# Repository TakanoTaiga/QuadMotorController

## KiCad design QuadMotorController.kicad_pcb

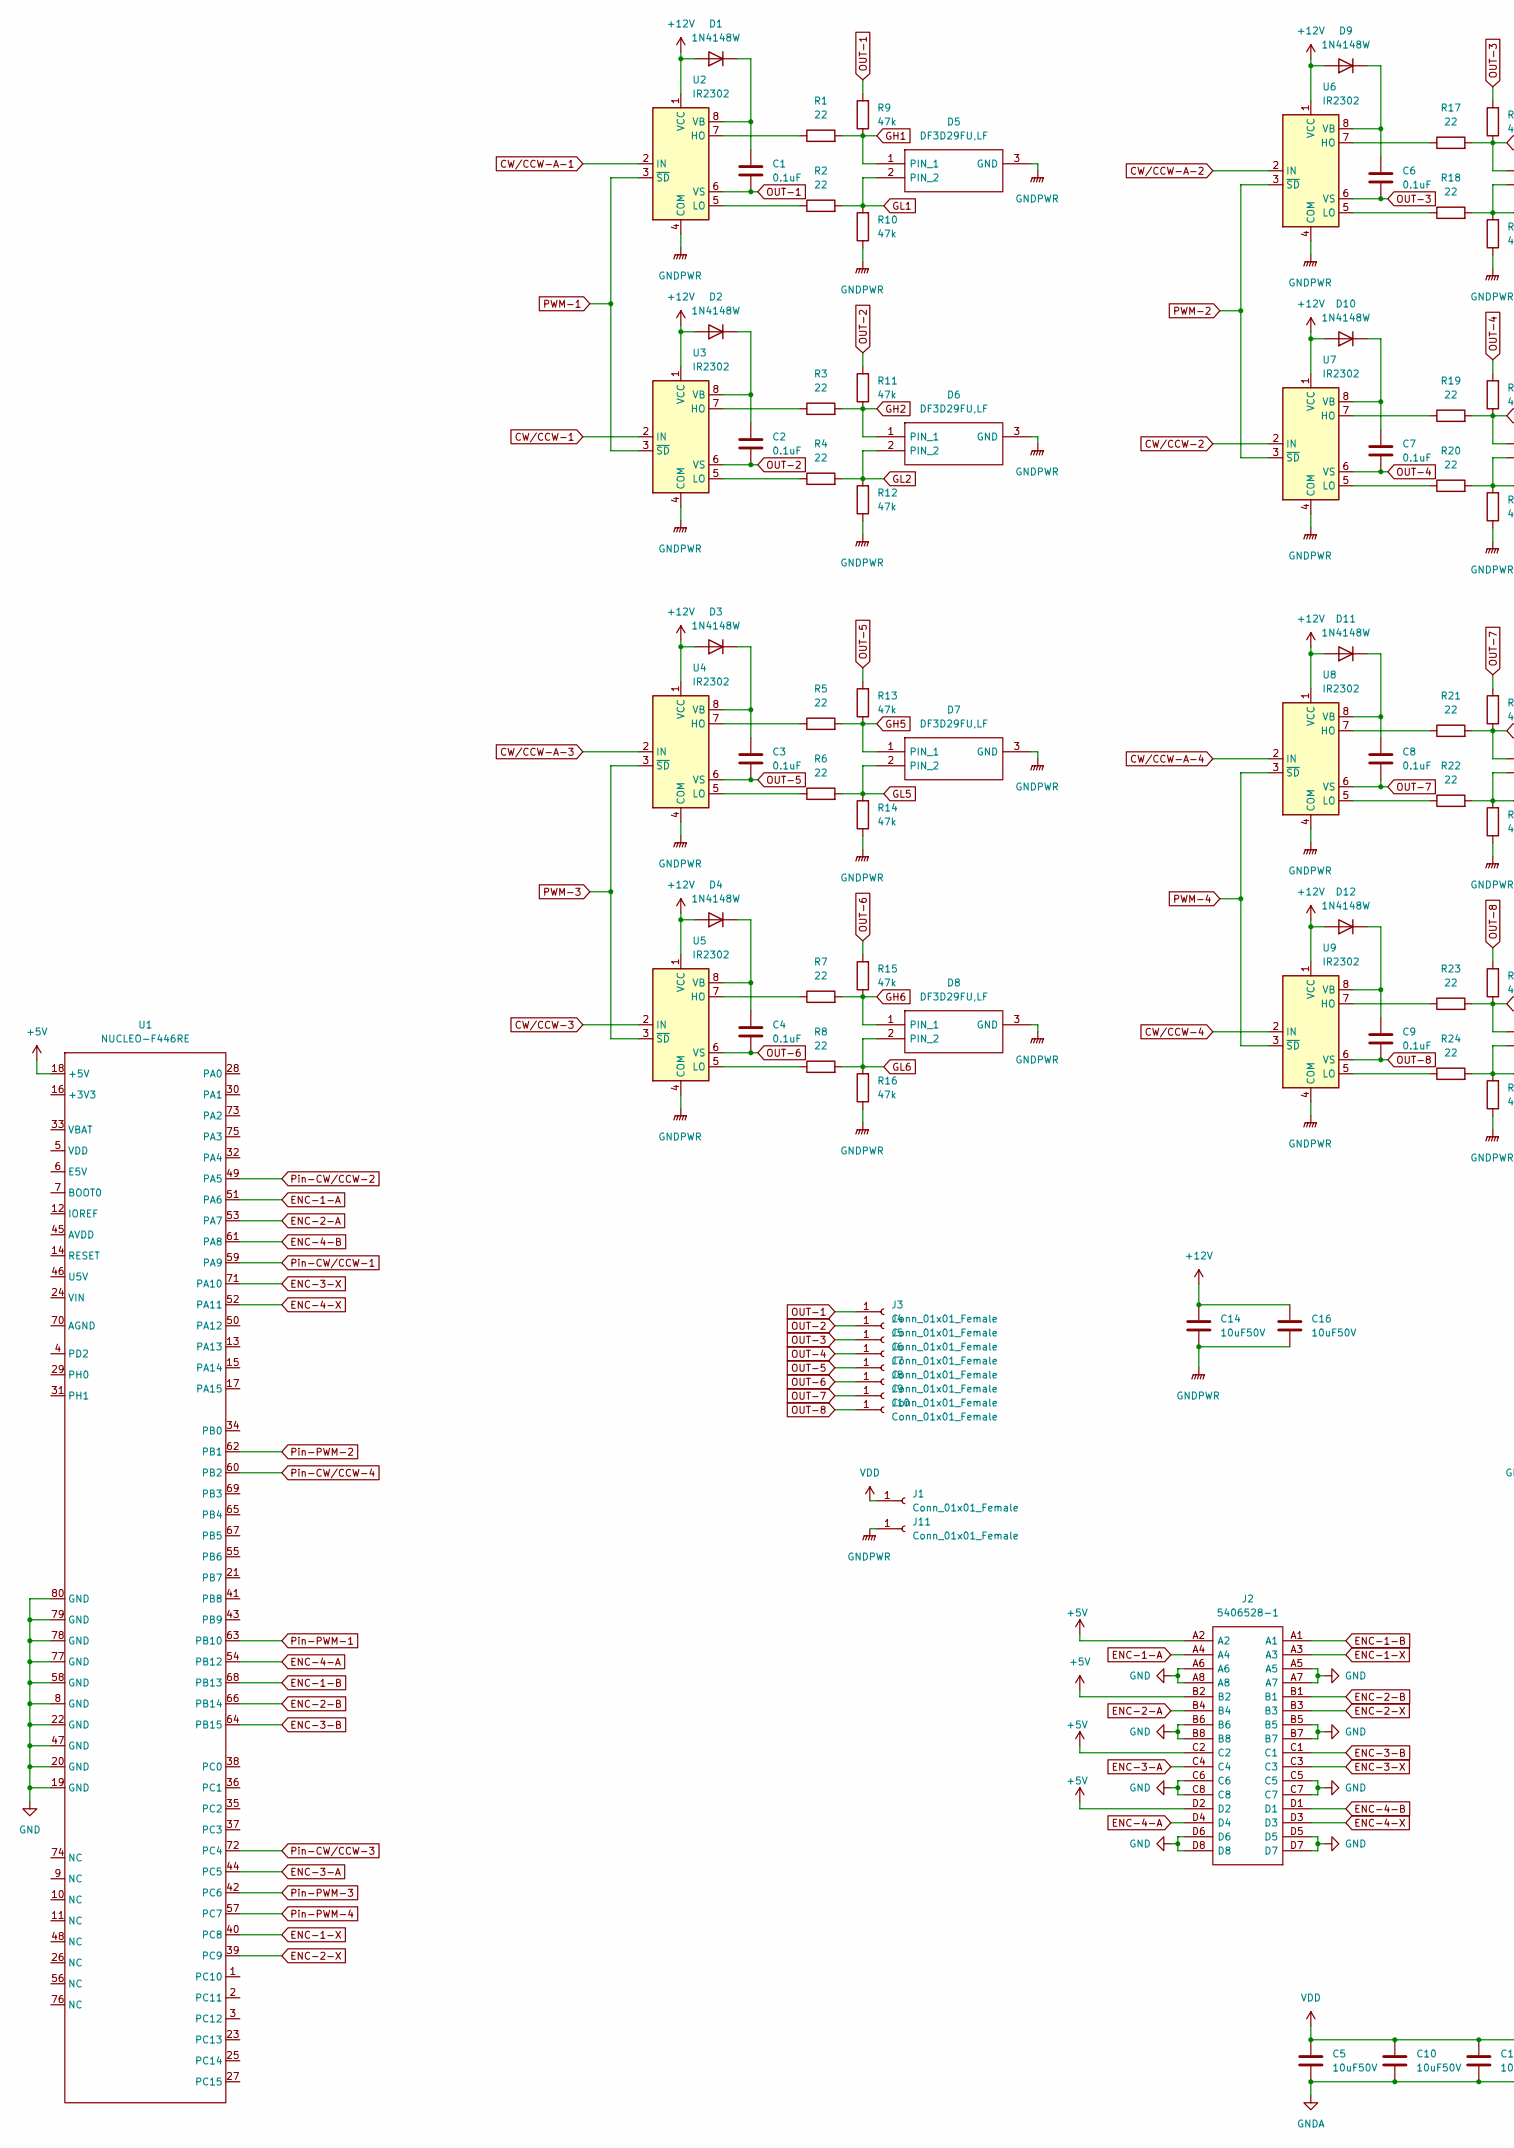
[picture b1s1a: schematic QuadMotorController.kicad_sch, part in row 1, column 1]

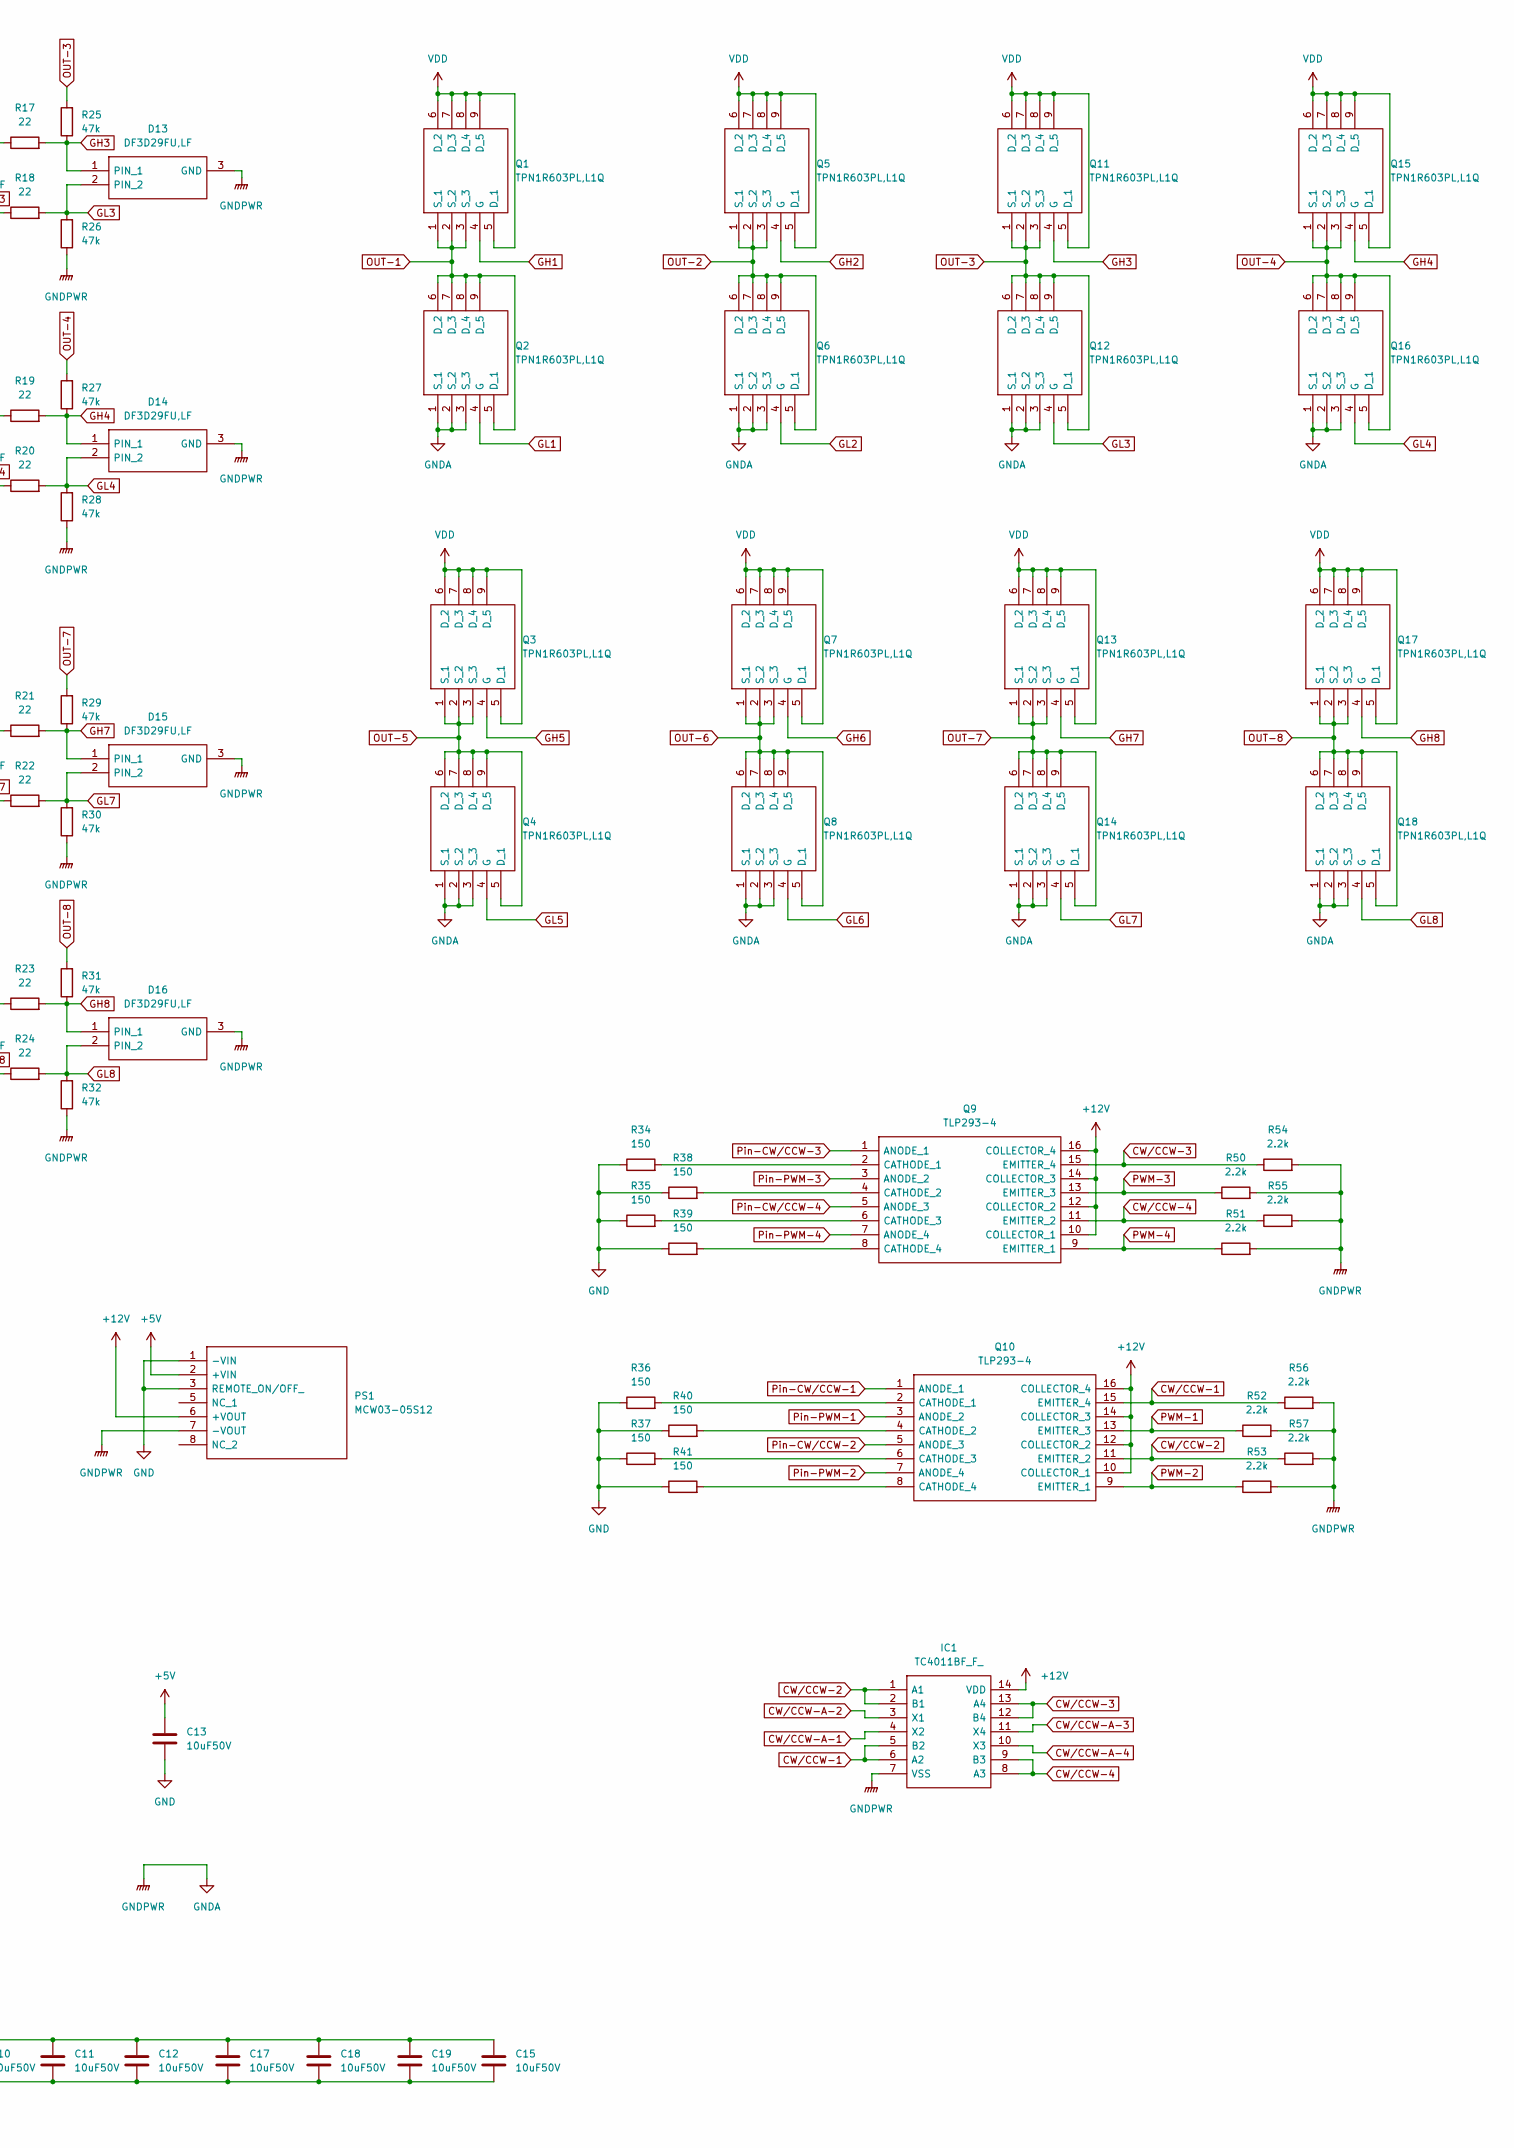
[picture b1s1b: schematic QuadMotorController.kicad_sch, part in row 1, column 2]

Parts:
C1, C2, C3, C4, C6, C7, C8, C9: 0.1uF; C_0805_2012Metric
C5, C10, C11, C12, C14, C15, C16, C17, C18, C19: 10uF50V; C_1206_3216Metric
C13: 10uF50V; C_0805_2012Metric
D1, D2, D3, D4, D9, D10, D11, D12: 1N4148W; D_SOD-123
D5, D6, D7, D8, D13, D14, D15, D16: DF3D29FU,LF; DF3D29FULF; Manufacturer_Part_Number DF3D29FU,LF
IC1: TC4011BF_F_; SOIC127P780X190-14N; Manufacturer_Part_Number TC4011BF(F)
J1, J3, J4, J5, J6, J7, J8, J9, J10, J11: Conn_01x01_Female; Pin1
J2: 5406528-1; 54065281; Manufacturer_Part_Number 5406528-1
PS1: MCW03-05S12; MCW0305S12; Manufacturer_Part_Number MCW03-05S12
Q1, Q2, Q3, Q4, Q5, Q6, Q7, Q8, Q11, Q12, Q13, Q14, Q15, Q16, Q17, Q18: TPN1R603PL,L1Q; TPN1R603PLL1Q; Manufacturer_Part_Number TPN1R603PL,L1Q
Q9, Q10: TLP293-4; SOIC127P700X230-16N; Manufacturer_Part_Number TLP293-4
R1, R2, R3, R4, R5, R6, R7, R8, R17, R18, R19, R20, R21, R22, R23, R24: 22; R_0603_1608Metric
R9, R10, R11, R12, R13, R14, R15, R16, R25, R26, R27, R28, R29, R30, R31, R32: 47k; R_0603_1608Metric
R34, R35, R36, R37, R38, R39, R40, R41: 150; R_0603_1608Metric
R50, R51, R52, R53, R54, R55, R56, R57: 2.2k; R_0603_1608Metric
U1: NUCLEO-F446RE
U2, U3, U4, U5, U6, U7, U8, U9: IR2302; SOP-8_3.9x4.9mm_P1.27mm

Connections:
+5V: C13.1, J2.A2, J2.B2, J2.C2, J2.D2, PS1.2 (+VIN), U1.18 (+5V)
+12V: C14.1, C16.1, D1.2 (A), D2.2 (A), D3.2 (A), D4.2 (A), D9.2 (A), D10.2 (A), D11.2 (A), D12.2 (A), IC1.14 (VDD), PS1.6 (+VOUT), Q9.10 (COLLECTOR_1), Q9.12 (COLLECTOR_2), Q9.14 (COLLECTOR_3), Q9.16 (COLLECTOR_4), Q10.10 (COLLECTOR_1), Q10.12 (COLLECTOR_2), Q10.14 (COLLECTOR_3), Q10.16 (COLLECTOR_4), U2.1 (VCC), U3.1 (VCC), U4.1 (VCC), U5.1 (VCC), U6.1 (VCC), U7.1 (VCC), U8.1 (VCC), U9.1 (VCC)
CW/CCW-1: IC1.5 (B2), IC1.6 (A2), Q10.15 (EMITTER_4), R56.1, U3.2 (IN)
CW/CCW-2: IC1.1 (A1), IC1.2 (B1), Q10.11 (EMITTER_2), R57.1, U7.2 (IN)
CW/CCW-3: IC1.12 (B4), IC1.13 (A4), Q9.15 (EMITTER_4), R54.1, U5.2 (IN)
CW/CCW-4: IC1.8 (A3), IC1.9 (B3), Q9.11 (EMITTER_2), R55.1, U9.2 (IN)
CW/CCW-A-1: IC1.4 (X2), U2.2 (IN)
CW/CCW-A-2: IC1.3 (X1), U6.2 (IN)
CW/CCW-A-3: IC1.11 (X4), U4.2 (IN)
CW/CCW-A-4: IC1.10 (X3), U8.2 (IN)
ENC-1-A: J2.A4, U1.51 (PA6)
ENC-1-B: J2.A1, U1.68 (PB13)
ENC-1-X: J2.A3, U1.40 (PC8)
ENC-2-A: J2.B4, U1.53 (PA7)
ENC-2-B: J2.B1, U1.66 (PB14)
ENC-2-X: J2.B3, U1.39 (PC9)
ENC-3-A: J2.C4, U1.44 (PC5)
ENC-3-B: J2.C1, U1.64 (PB15)
ENC-3-X: J2.C3, U1.71 (PA10)
ENC-4-A: J2.D4, U1.54 (PB12)
ENC-4-B: J2.D1, U1.61 (PA8)
ENC-4-X: J2.D3, U1.52 (PA11)
GH1: D5.1 (PIN_1), Q1.4 (G), R1.2, R9.1
GH2: D6.1 (PIN_1), Q5.4 (G), R3.2, R11.1
GH3: D13.1 (PIN_1), Q11.4 (G), R17.2, R25.1
GH4: D14.1 (PIN_1), Q15.4 (G), R19.2, R27.1
GH5: D7.1 (PIN_1), Q3.4 (G), R5.2, R13.1
GH6: D8.1 (PIN_1), Q7.4 (G), R7.2, R15.1
GH7: D15.1 (PIN_1), Q13.4 (G), R21.2, R29.1
GH8: D16.1 (PIN_1), Q17.4 (G), R23.2, R31.1
GL1: D5.2 (PIN_2), Q2.4 (G), R2.2, R10.2
GL2: D6.2 (PIN_2), Q6.4 (G), R4.2, R12.2
GL3: D13.2 (PIN_2), Q12.4 (G), R18.2, R26.2
GL4: D14.2 (PIN_2), Q16.4 (G), R20.2, R28.2
GL5: D7.2 (PIN_2), Q4.4 (G), R6.2, R14.2
GL6: D8.2 (PIN_2), Q8.4 (G), R8.2, R16.2
GL7: D15.2 (PIN_2), Q14.4 (G), R22.2, R30.2
GL8: D16.2 (PIN_2), Q18.4 (G), R24.2, R32.2
GND: C13.2, J2.A5, J2.A6, J2.A7, J2.A8, J2.B5, J2.B6, J2.B7, J2.B8, J2.C5, J2.C6, J2.C7, J2.C8, J2.D5, J2.D6, J2.D7, J2.D8, PS1.1 (-VIN), PS1.3 (REMOTE_ON/OFF_), R34.1, R35.1, R36.1, R37.1, R38.1, R39.1, R40.1, R41.1, U1.8 (GND), U1.19 (GND), U1.20 (GND), U1.22 (GND), U1.47 (GND), U1.58 (GND), U1.77 (GND), U1.78 (GND), U1.79 (GND), U1.80 (GND)
GNDA: C5.2, C10.2, C11.2, C12.2, C14.2, C15.2, C16.2, C17.2, C18.2, C19.2, D5.3 (GND), D6.3 (GND), D7.3 (GND), D8.3 (GND), D13.3 (GND), D14.3 (GND), D15.3 (GND), D16.3 (GND), IC1.7 (VSS), J11.1, PS1.7 (-VOUT), Q2.1 (S_1), Q2.2 (S_2), Q2.3 (S_3), Q4.1 (S_1), Q4.2 (S_2), Q4.3 (S_3), Q6.1 (S_1), Q6.2 (S_2), Q6.3 (S_3), Q8.1 (S_1), Q8.2 (S_2), Q8.3 (S_3), Q12.1 (S_1), Q12.2 (S_2), Q12.3 (S_3), Q14.1 (S_1), Q14.2 (S_2), Q14.3 (S_3), Q16.1 (S_1), Q16.2 (S_2), Q16.3 (S_3), Q18.1 (S_1), Q18.2 (S_2), Q18.3 (S_3), R10.1, R12.1, R14.1, R16.1, R26.1, R28.1, R30.1, R32.1, R50.2, R51.2, R52.2, R53.2, R54.2, R55.2, R56.2, R57.2, U2.4 (COM), U3.4 (COM), U4.4 (COM), U5.4 (COM), U6.4 (COM), U7.4 (COM), U8.4 (COM), U9.4 (COM)
unnamed: C1.1, D1.1 (K), U2.8 (VB)
unnamed: C2.1, D2.1 (K), U3.8 (VB)
unnamed: C3.1, D3.1 (K), U4.8 (VB)
unnamed: C4.1, D4.1 (K), U5.8 (VB)
unnamed: C6.1, D9.1 (K), U6.8 (VB)
unnamed: C7.1, D10.1 (K), U7.8 (VB)
unnamed: C8.1, D11.1 (K), U8.8 (VB)
unnamed: C9.1, D12.1 (K), U9.8 (VB)
unnamed: Q9.2 (CATHODE_1), R34.2
unnamed: Q9.4 (CATHODE_2), R38.2
unnamed: Q9.6 (CATHODE_3), R35.2
unnamed: Q9.8 (CATHODE_4), R39.2
unnamed: Q10.2 (CATHODE_1), R36.2
unnamed: Q10.4 (CATHODE_2), R40.2
unnamed: Q10.6 (CATHODE_3), R37.2
unnamed: Q10.8 (CATHODE_4), R41.2
unnamed: R1.1, U2.7 (HO)
unnamed: R2.1, U2.5 (LO)
unnamed: R3.1, U3.7 (HO)
unnamed: R4.1, U3.5 (LO)
unnamed: R5.1, U4.7 (HO)
unnamed: R6.1, U4.5 (LO)
unnamed: R7.1, U5.7 (HO)
unnamed: R8.1, U5.5 (LO)
unnamed: R17.1, U6.7 (HO)
unnamed: R18.1, U6.5 (LO)
unnamed: R19.1, U7.7 (HO)
unnamed: R20.1, U7.5 (LO)
unnamed: R21.1, U8.7 (HO)
unnamed: R22.1, U8.5 (LO)
unnamed: R23.1, U9.7 (HO)
unnamed: R24.1, U9.5 (LO)
OUT-1: C1.2, J3.1, Q1.1 (S_1), Q1.2 (S_2), Q1.3 (S_3), Q2.5 (D_1), Q2.6 (D_2), Q2.7 (D_3), Q2.8 (D_4), Q2.9 (D_5), R9.2, U2.6 (VS)
OUT-2: C2.2, J4.1, Q5.1 (S_1), Q5.2 (S_2), Q5.3 (S_3), Q6.5 (D_1), Q6.6 (D_2), Q6.7 (D_3), Q6.8 (D_4), Q6.9 (D_5), R11.2, U3.6 (VS)
OUT-3: C6.2, J5.1, Q11.1 (S_1), Q11.2 (S_2), Q11.3 (S_3), Q12.5 (D_1), Q12.6 (D_2), Q12.7 (D_3), Q12.8 (D_4), Q12.9 (D_5), R25.2, U6.6 (VS)
OUT-4: C7.2, J6.1, Q15.1 (S_1), Q15.2 (S_2), Q15.3 (S_3), Q16.5 (D_1), Q16.6 (D_2), Q16.7 (D_3), Q16.8 (D_4), Q16.9 (D_5), R27.2, U7.6 (VS)
OUT-5: C3.2, J7.1, Q3.1 (S_1), Q3.2 (S_2), Q3.3 (S_3), Q4.5 (D_1), Q4.6 (D_2), Q4.7 (D_3), Q4.8 (D_4), Q4.9 (D_5), R13.2, U4.6 (VS)
OUT-6: C4.2, J8.1, Q7.1 (S_1), Q7.2 (S_2), Q7.3 (S_3), Q8.5 (D_1), Q8.6 (D_2), Q8.7 (D_3), Q8.8 (D_4), Q8.9 (D_5), R15.2, U5.6 (VS)
OUT-7: C8.2, J9.1, Q13.1 (S_1), Q13.2 (S_2), Q13.3 (S_3), Q14.5 (D_1), Q14.6 (D_2), Q14.7 (D_3), Q14.8 (D_4), Q14.9 (D_5), R29.2, U8.6 (VS)
OUT-8: C9.2, J10.1, Q17.1 (S_1), Q17.2 (S_2), Q17.3 (S_3), Q18.5 (D_1), Q18.6 (D_2), Q18.7 (D_3), Q18.8 (D_4), Q18.9 (D_5), R31.2, U9.6 (VS)
PWM-1: Q10.13 (EMITTER_3), R52.1, U2.3 (~SD), U3.3 (~SD)
PWM-2: Q10.9 (EMITTER_1), R53.1, U6.3 (~SD), U7.3 (~SD)
PWM-3: Q9.13 (EMITTER_3), R50.1, U4.3 (~SD), U5.3 (~SD)
PWM-4: Q9.9 (EMITTER_1), R51.1, U8.3 (~SD), U9.3 (~SD)
Pin-CW/CCW-1: Q10.1 (ANODE_1), U1.59 (PA9)
Pin-CW/CCW-2: Q10.5 (ANODE_3), U1.49 (PA5)
Pin-CW/CCW-3: Q9.1 (ANODE_1), U1.72 (PC4)
Pin-CW/CCW-4: Q9.5 (ANODE_3), U1.60 (PB2)
Pin-PWM-1: Q10.3 (ANODE_2), U1.63 (PB10)
Pin-PWM-2: Q10.7 (ANODE_4), U1.62 (PB1)
Pin-PWM-3: Q9.3 (ANODE_2), U1.42 (PC6)
Pin-PWM-4: Q9.7 (ANODE_4), U1.57 (PC7)
VDD: C5.1, C10.1, C11.1, C12.1, C15.1, C17.1, C18.1, C19.1, J1.1, Q1.5 (D_1), Q1.6 (D_2), Q1.7 (D_3), Q1.8 (D_4), Q1.9 (D_5), Q3.5 (D_1), Q3.6 (D_2), Q3.7 (D_3), Q3.8 (D_4), Q3.9 (D_5), Q5.5 (D_1), Q5.6 (D_2), Q5.7 (D_3), Q5.8 (D_4), Q5.9 (D_5), Q7.5 (D_1), Q7.6 (D_2), Q7.7 (D_3), Q7.8 (D_4), Q7.9 (D_5), Q11.5 (D_1), Q11.6 (D_2), Q11.7 (D_3), Q11.8 (D_4), Q11.9 (D_5), Q13.5 (D_1), Q13.6 (D_2), Q13.7 (D_3), Q13.8 (D_4), Q13.9 (D_5), Q15.5 (D_1), Q15.6 (D_2), Q15.7 (D_3), Q15.8 (D_4), Q15.9 (D_5), Q17.5 (D_1), Q17.6 (D_2), Q17.7 (D_3), Q17.8 (D_4), Q17.9 (D_5)

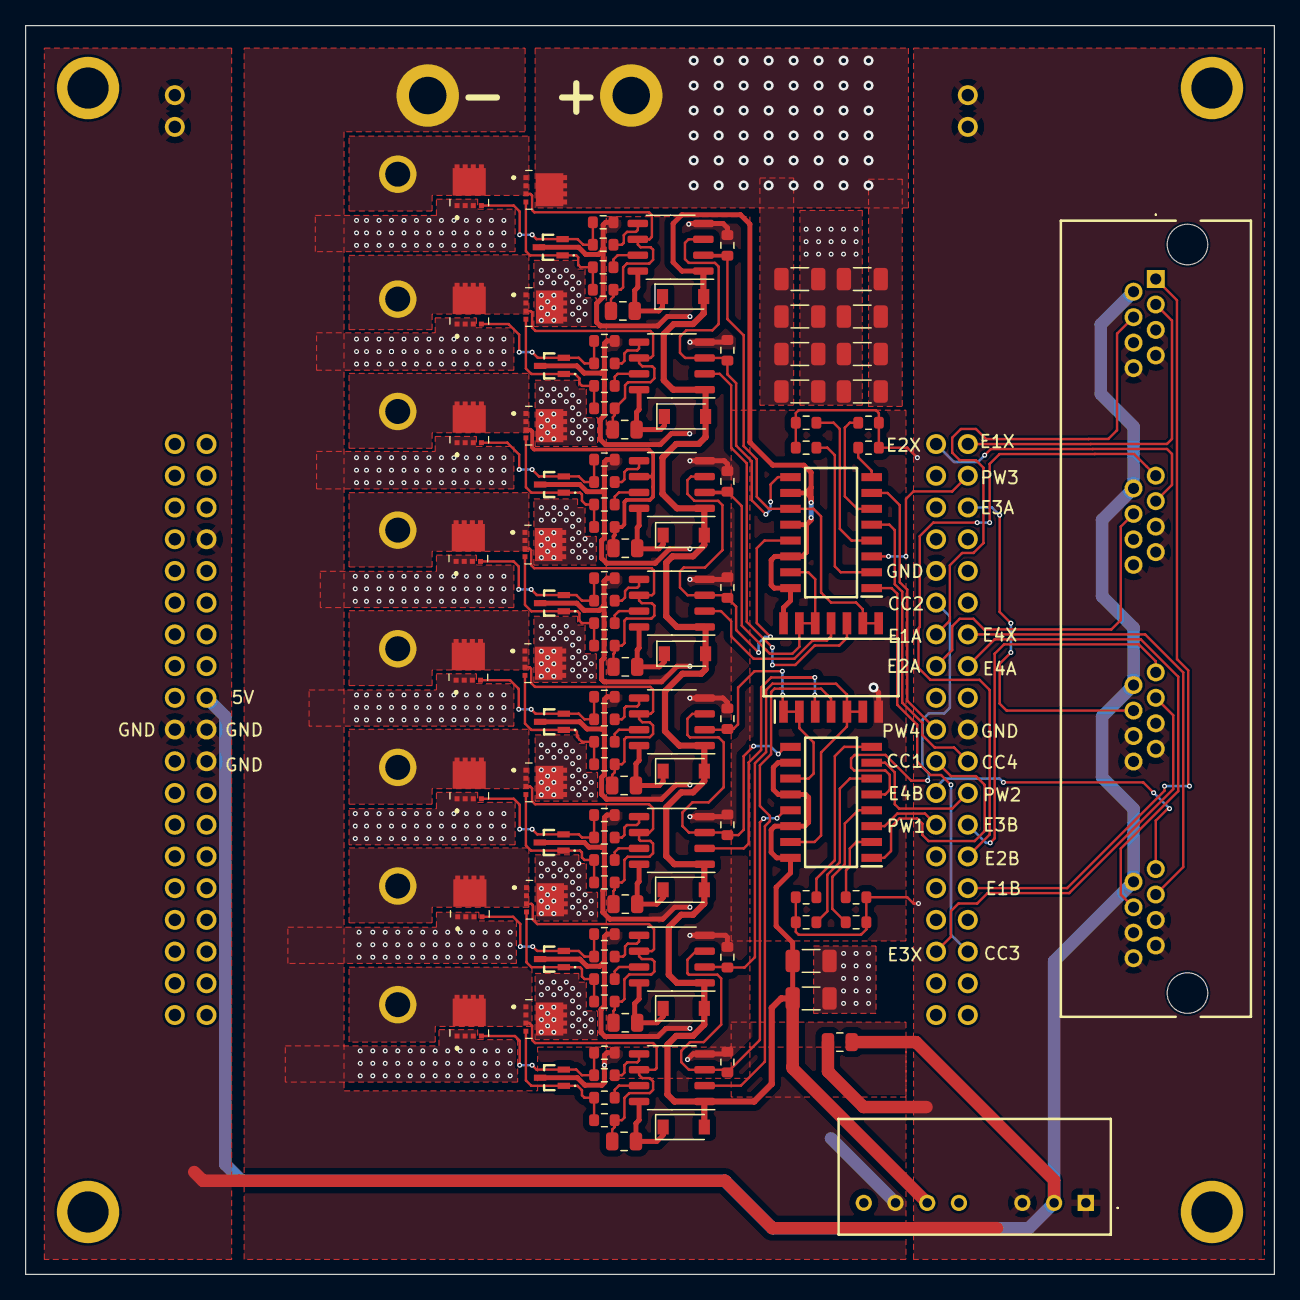
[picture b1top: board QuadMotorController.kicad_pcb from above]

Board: 2 copper layers, 100.0 x 100.0 mm, 123 parts (0 on the bottom side), 93 nets.

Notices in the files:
QuadMotorController.kicad_pcb:
Copyright © 2022 Hakodate Roboken. All rights reserved.
